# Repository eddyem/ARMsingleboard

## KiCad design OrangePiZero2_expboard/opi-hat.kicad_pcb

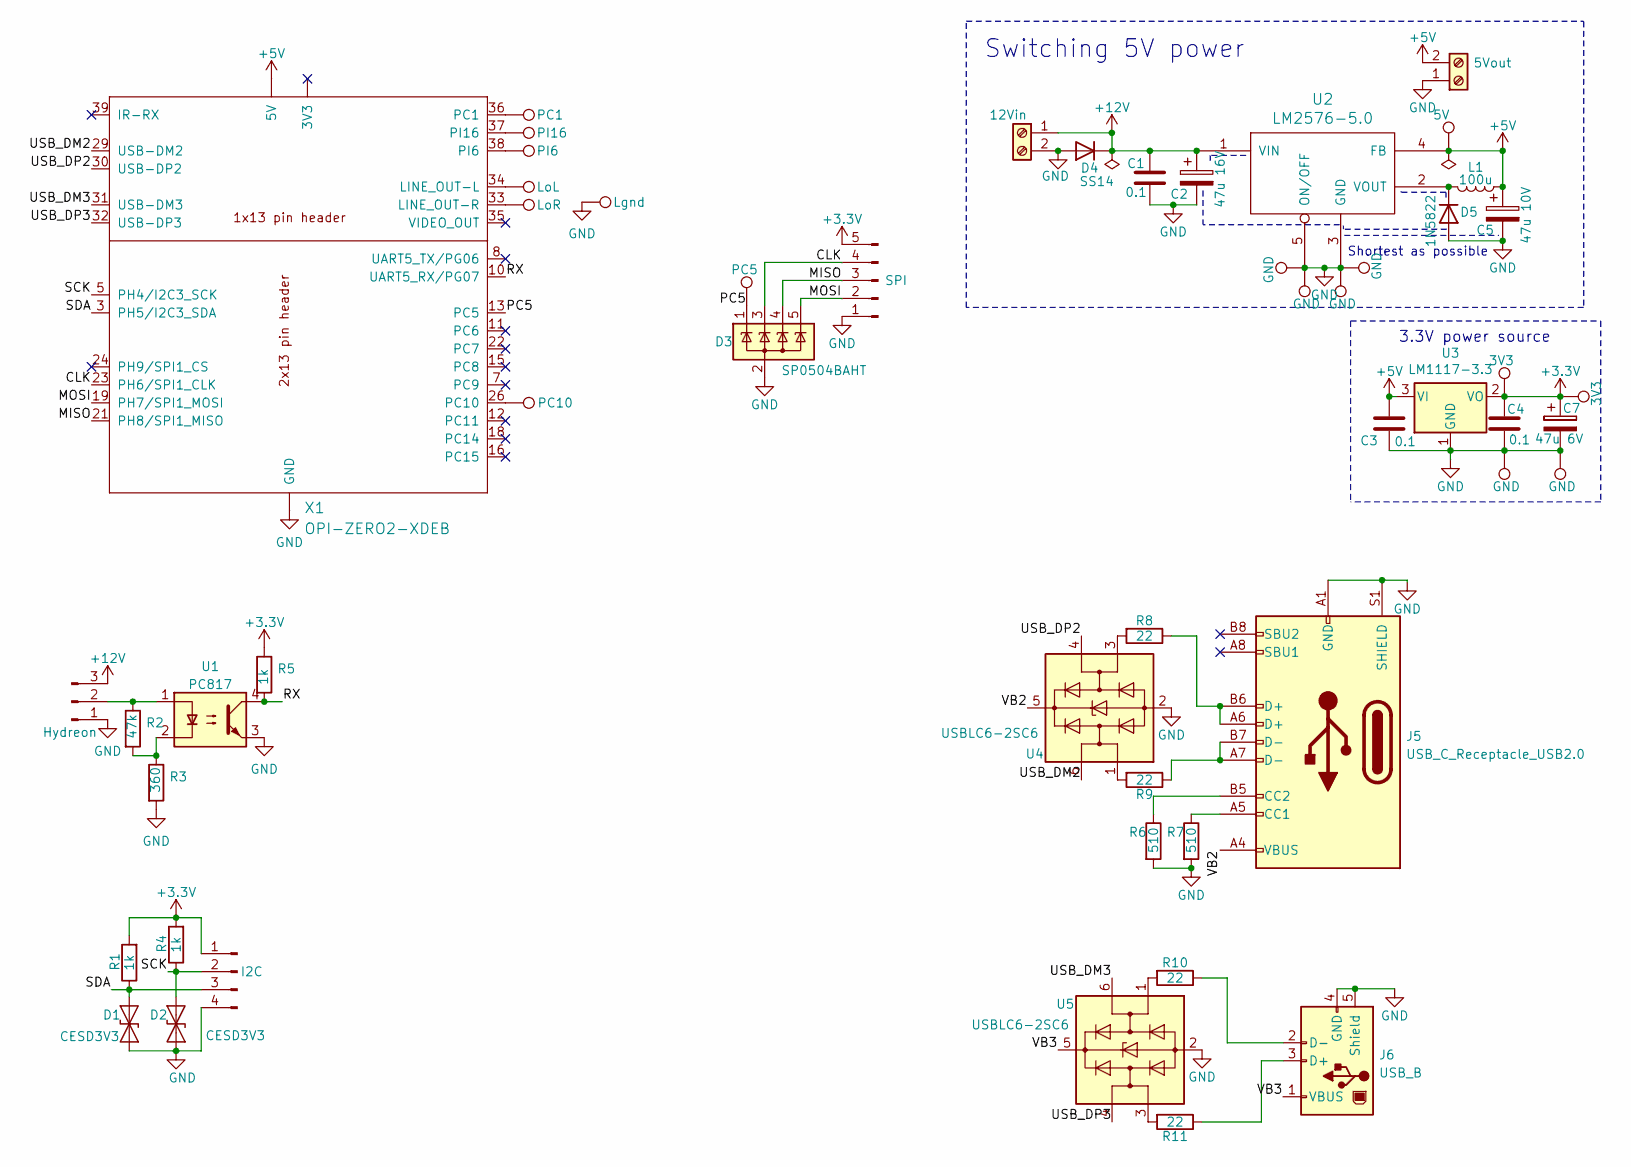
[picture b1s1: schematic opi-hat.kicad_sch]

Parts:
C1, C3, C4: 0.1; C_0603_1608Metric_Pad1.08x0.95mm_HandSolder
C2: 47u 16V; CP_EIA-6032-28_Kemet-C_Pad2.25x2.35mm_HandSolder
C5: 47u 10V; CP_EIA-6032-28_Kemet-C_Pad2.25x2.35mm_HandSolder
C7: 47u 6V; CP_EIA-3216-18_Kemet-A_Pad1.58x1.35mm_HandSolder
D1, D2: CESD3V3; D_SOD-323_HandSoldering
D3: SP0504BAHT; SOT-23-5
D4: SS14; D_SMA-SMB_Universal_Handsoldering
D5: 1N5822; D_DO-201_P3.81mm_Vertical_AnodeUp
J1: Hydreon; JST_PH_B3B-PH-K_1x03_P2.00mm_Vertical
J2: I2C; JST_PH_B4B-PH-K_1x04_P2.00mm_Vertical
J3: SPI; JST_PH_B5B-PH-K_1x05_P2.00mm_Vertical
J4: 12Vin; TerminalBlock_Phoenix_MKDS-1,5-2_1x02_P5.00mm_Horizontal
J5: USB_C_Receptacle_USB2.0; USB_C_Receptacle_HRO_TYPE-C-31-M-12
J6: USB_B; USB_Mini-B_Wuerth_65100516121_Horizontal
J7: 5Vout; JST_PH_B2B-PH-K_1x02_P2.00mm_Vertical
L1: 100u; L_Toroid_Horizontal_D6.5mm_P10.00mm_Diameter7-5mm_Amidon-T25
R1, R4, R5: 1k; R_0603_1608Metric_Pad0.98x0.95mm_HandSolder
R2: 47k; R_0603_1608Metric_Pad0.98x0.95mm_HandSolder
R3: 360; R_0603_1608Metric_Pad0.98x0.95mm_HandSolder
R6, R7: 510; R_0603_1608Metric_Pad0.98x0.95mm_HandSolder
R8, R9, R10, R11: 22; R_0603_1608Metric_Pad0.98x0.95mm_HandSolder
TP1, TP2, TP13, TP14, TP15, TP17: GND; TestPoint_THTPad_2.5x2.5mm_Drill1.2mm
TP3: 5V; TestPoint_THTPad_2.5x2.5mm_Drill1.2mm
TP4, TP16: 3V3; TestPoint_THTPad_2.5x2.5mm_Drill1.2mm
TP5: PC10; TestPoint_THTPad_2.5x2.5mm_Drill1.2mm
TP6: PC1; TestPoint_THTPad_2.5x2.5mm_Drill1.2mm
TP7: PC5; TestPoint_THTPad_2.5x2.5mm_Drill1.2mm
TP8: PI6; TestPoint_THTPad_2.5x2.5mm_Drill1.2mm
TP9: PI16; TestPoint_THTPad_2.5x2.5mm_Drill1.2mm
TP10: LoL; TestPoint_THTPad_1.0x1.0mm_Drill0.5mm
TP11: LoR; TestPoint_THTPad_1.0x1.0mm_Drill0.5mm
TP12: Lgnd; TestPoint_THTPad_1.0x1.0mm_Drill0.5mm
U1: PC817; DIP-4_W7.62mm
U2: LM2576-5.0; TO-263-5_TabPin3
U3: LM1117-3.3; SOT-223-3_TabPin2
U4, U5: USBLC6-2SC6; SOT-23-6_Handsoldering
X1: OPI-ZERO2-XDEB; OPIZ2HAT

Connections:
+3.3V: C4.1, C7.1, J2.1, J3.5, R1.2, R4.2, R5.1, TP4.1, TP16.1, U3.2 (VO)
+5V: C3.1, C5.1, J7.2, L1.1, TP3.1, U2.4 (FB), U3.3 (VI), X1.2 (5V), X1.4 (5V), X1.27 (5V)
+12V: C1.1, C2.1, D4.1 (K), J1.3, J4.1, U2.1 (VIN)
/CLK: D3.3 (K), J3.4, X1.23 (PH6/SPI1_CLK)
/MISO: D3.4 (K), J3.3, X1.21 (PH8/SPI1_MISO)
/MOSI: D3.5 (K), J3.2, X1.19 (PH7/SPI1_MOSI)
/PC5: D3.1 (K), TP7.1, X1.13 (PC5)
/RX: R5.2, U1.4, X1.10 (UART5_RX/PG07)
/SCK: D2.1 (A1), J2.2, R4.1, X1.5 (PH4/I2C3_SCK)
/SDA: D1.1 (A1), J2.3, R1.1, X1.3 (PH5/I2C3_SDA)
/USB_DM2: U4.6 (I/O1), X1.29 (USB-DM2)
/USB_DM3: U5.6 (I/O1), X1.31 (USB-DM3)
/USB_DP2: U4.4 (I/O2), X1.30 (USB-DP2)
/USB_DP3: U5.4 (I/O2), X1.32 (USB-DP3)
/VB2: J5.A4 (VBUS), J5.A9 (VBUS), J5.B4 (VBUS), J5.B9 (VBUS), U4.5 (VBUS)
/VB3: J6.1 (VBUS), U5.5 (VBUS)
GND: C1.2, C2.2, C3.2, C4.2, C5.2, C7.2, D1.2 (A2), D2.2 (A2), D3.2 (A), D4.2 (A), D5.2 (A), J1.1, J2.4, J3.1, J4.2, J5.A1 (GND), J5.A12 (GND), J5.B1 (GND), J5.B12 (GND), J5.S1 (SHIELD), J6.4 (GND), J6.5 (Shield), J7.1, R3.2, R6.2, R7.2, TP1.1, TP2.1, TP12.1, TP13.1, TP14.1, TP15.1, TP17.1, U1.3, U2.3 (GND), U2.5 (ON/OFF), U3.1 (GND), U4.2 (GND), U5.2 (GND), X1.6 (GND), X1.9 (GND), X1.14 (GND), X1.20 (GND), X1.25 (GND), X1.28 (GND)
unnamed: D5.1 (K), L1.2, U2.2 (VOUT)
unnamed: J1.2, R2.1, U1.1
unnamed: J5.A5 (CC1), R7.1
unnamed: J5.A6 (D+), J5.B6 (D+), R8.1
unnamed: J5.A7 (D-), J5.B7 (D-), R9.1
unnamed: J5.B5 (CC2), R6.1
unnamed: J6.2 (D-), R10.1
unnamed: J6.3 (D+), R11.1
unnamed: R2.2, R3.1, U1.2
unnamed: R8.2, U4.3 (I/O2)
unnamed: R9.2, U4.1 (I/O1)
unnamed: R10.2, U5.1 (I/O1)
unnamed: R11.2, U5.3 (I/O2)
unnamed: TP5.1, X1.26 (PC10)
unnamed: TP6.1, X1.36 (PC1)
unnamed: TP8.1, X1.38 (PI6)
unnamed: TP9.1, X1.37 (PI16)
unnamed: TP10.1, X1.34 (LINE_OUT-L)
unnamed: TP11.1, X1.33 (LINE_OUT-R)

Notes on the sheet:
Switching 5V power
3.3V power source
Shortest as possible

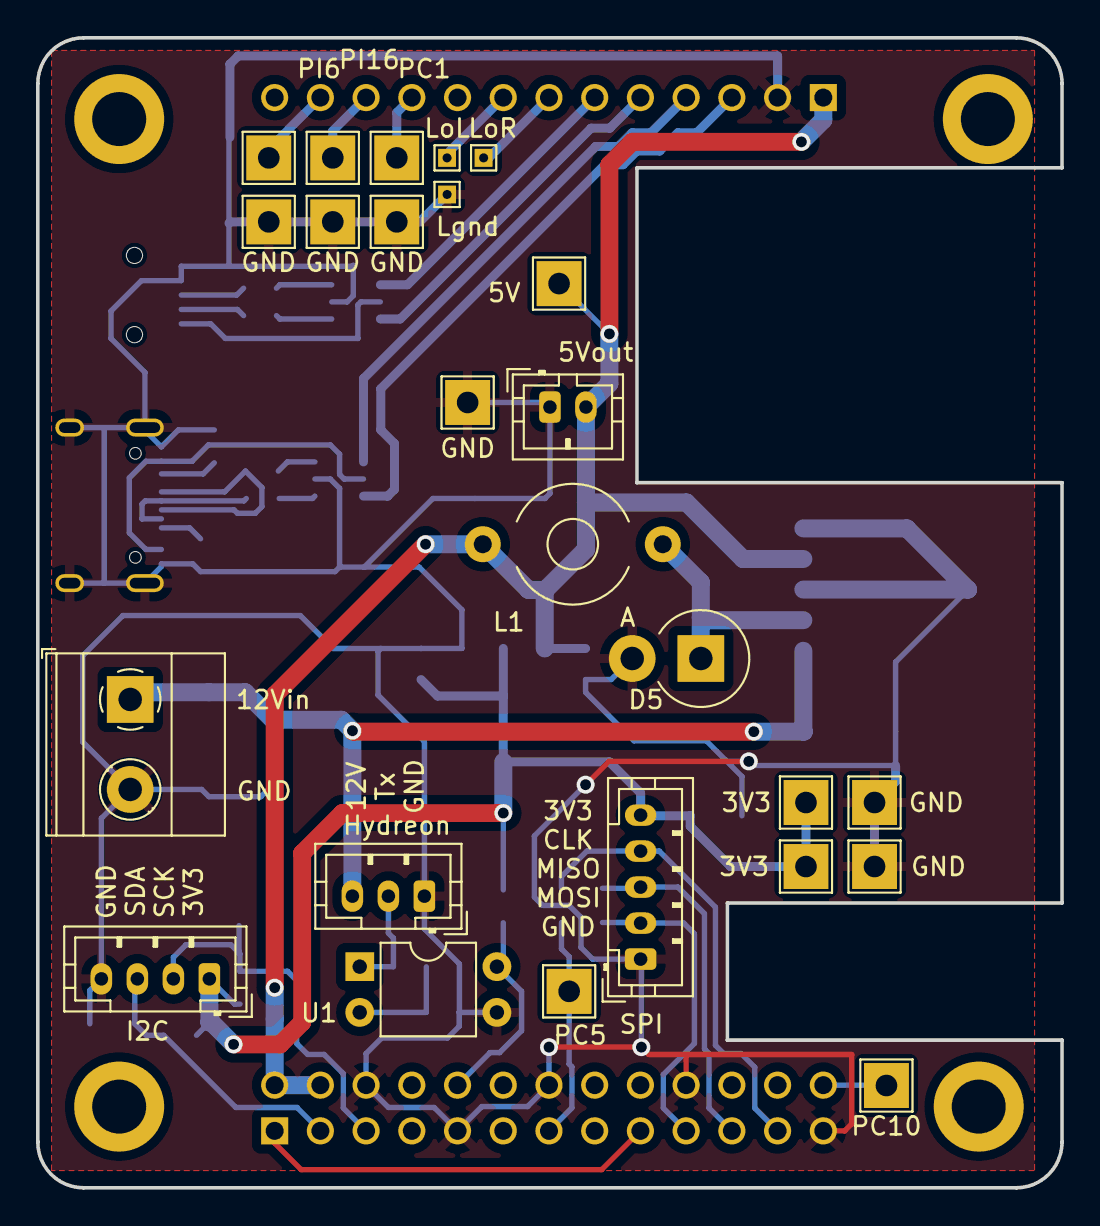
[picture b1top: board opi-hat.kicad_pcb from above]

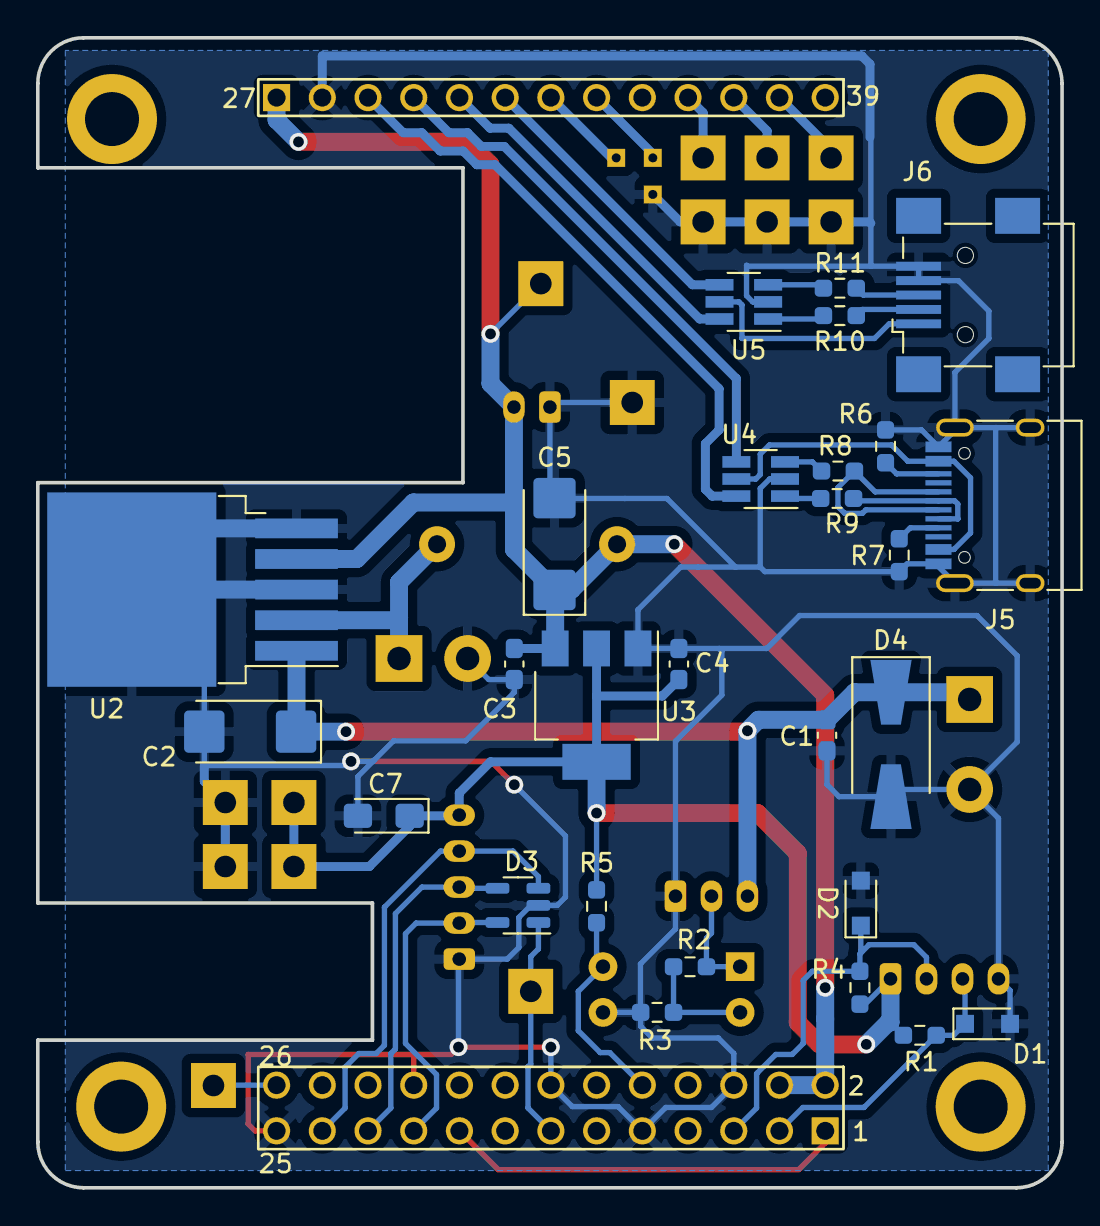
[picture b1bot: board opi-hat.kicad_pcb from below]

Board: 2 copper layers, 56.9 x 63.9 mm, 53 parts (27 on the bottom side), 36 nets.

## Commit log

2022-09-27 add I2C, BMP180, MLX90640
2022-09-29 add expansion boards for Opiz & Opiz2
2022-09-29 add si/htu
2022-10-01 add bmpe280
2023-02-04 some changes in MLX90640, add scripts
2023-06-30 add GPIO management over etrhernet
2023-07-05 invert GPIO output (due to active LOW)
2024-03-12 fixed boards on new kicad
2024-06-05 add simplest barrier management
2024-06-17 seems like it works
2024-08-20 Starting AS3935
2024-08-21 More code, but sensor seems dead: don't run antenna
